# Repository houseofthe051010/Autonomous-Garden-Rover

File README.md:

# Autonomous Garden Rover

This is an open source outdoor garden robot that can mow grass and water plants for under $500. It features a powerful 3000 watt C6374 motor for mowing grass with electronic height control, and a large Nema17 turret system for watering at target places that supports a normal garden hose. The rover currently uses a 9 axis IMU + wheel encoders for autonomous function. The brain of this rover is a powerful ESP32-P4, which gives this rover the capability to listen and respond to commands using its built in microphone and speaker.

## Inspiration

I spend hours each week gardening and mowing grass. As someone into robotics, I realized I could build a garden rover to automate some of these repetitive chores. This project gave me a reason to learn more about robotics while building something useful for my yard.

[**Watch the full rover demo**](https://youtu.be/P-olpegfmmU) · [**Forge journal**](https://forge.hackclub.com/projects/3732) · [**See the assembly**](CAD/) · [**Watch the firmware demo**](https://www.youtube.com/watch?v=vQ5m_EN1jJQ) 

### CAD Render Assembly

## Features

* Under $500, anyone can build it
* All four wheels are motorized
* C6374 Motor offers 3000W+ of power, more than most commercial systems
* Nema17 planetary motors lift and raise the mower using a rope system.
* The turret system uses high reduction worm + dual stage planetary drives to shoot water
* Has a microphone and speaker and can run small ai vision/text recognition models
* Water flow can be controlled using a seperate esp32 controller
* Can be controlled from a phone or handheld controller
* Uses a 9axis imu and encoders on all four wheels for precise autonomous
* The aluminum chassis bends and acts as a suspension
* Supports raspberry pi 5 with ROS 2 as brain
* Supports a custom hand held controller from my previous FPV claw drone project
* Advanced flexibility for conneting new sensors, cameras, and electronics
* Water resistant

# Building it yourself

Go to [**INSTRUCTIONS.md**](INSTRUCTIONS.md) to see the complete build instructions.

## Block schematic

This is a block level schematic of how each system is split

Kicad: [`Schematics/Block-level schematic/`](Schematics/Block-level%20schematic/).

## Bill of materials

| Item                                                         | Qty. | Unit price |       Total | Link                                                                                                                 |
| ------------------------------------------------------------ | ---: | ---------: | ----------: | -------------------------------------------------------------------------------------------------------------------- |
| Waveshare ESP32-P4-WIFI6 development board                   |    1 |     $26.87 |      $26.87 | [Amazon](https://www.amazon.com/dp/B0FM3SPXZG)                                                                       |
| Steelworks 3/4 in x 8 ft aluminum channel                    |    2 |     $19.98 |      $39.96 | [Lowe's](https://www.lowes.com/pd/Steelworks-3-4-in-W-x-8-ft-L-Mill-Finished-Aluminum-Weldable-Trim-Channel/3058185) |
| LGXSHOP C6374 170KV sensored BLDC motor                      |    1 |     $29.50 |      $29.50 | [Amazon](https://www.amazon.com/dp/B0GR88K1XP)                                                                       |
| STM32F103C6T6 Blue Pill development board                    |    1 |      $1.75 |       $1.75 | [AliExpress](https://www.aliexpress.us/item/3256809531654480.html)                                                   |
| BTS7960 high-current motor driver board                      |    2 |      $5.56 |      $11.12 | [AliExpress](https://www.aliexpress.us/item/3256812145540065.html)                                                   |
| DS3230 PRO drivetrain servo motors (4-pack)                  |    1 |     $41.37 |      $41.37 | [AliExpress](https://www.aliexpress.us/item/3256808314550897.html)                                                   |
| STEPPERONLINE NEMA 17 stepper motors (3-pack)                |    1 |     $25.99 |      $25.99 | [Amazon](https://www.amazon.com/dp/B0B38GHRH8)                                                                       |
| Stepper controller board (12-24 VDC)                         |    1 |     $22.99 |      $22.99 | [Amazon](https://www.amazon.com/dp/B0CCVSMGXR)                                                                       |
| EONO PETG 3D printer filament 1 kg black                     |    2 |      $9.99 |      $19.98 | [Amazon](https://www.amazon.com/EONO3D-Printer-Filament-1-75mm-2-2lbs/dp/B0G2BQQ5RT)                                 |
| 608 sealed steel bearings (20-pack)                          |    1 |      $4.99 |       $4.99 | [Amazon](https://www.amazon.com/dp/B0GX14YCFF)                                                                       |
| M3 screw kit (420-piece)                                     |    1 |      $8.98 |       $8.98 | [Amazon](https://www.amazon.com/dp/B0CSWD34KJ)                                                                       |
| Flipsky ODESC 56 V v4.2 single-axis controller               |    1 |     $39.99 |      $39.99 | [Amazon](https://www.amazon.com/dp/B0CB64MVHC)                                                                       |
| 22 AWG wire (10 m)                                           |    1 |      $2.81 |       $2.81 | [AliExpress](https://www.aliexpress.us/item/3256801511977665.html)                                                   |
| 36 V 10.4 Ah lithium battery with charger and XT60 connector |    1 |     $79.99 |      $79.99 | [eBay](https://www.ebay.com/itm/318206384216)                                                                        |
| 20 A buck converter                                          |    2 |      $3.58 |       $7.16 | [AliExpress](https://www.aliexpress.us/item/3256808333733098.html)                                                   |
| XL4005 buck converter                                        |    1 |      $1.99 |       $1.99 | [AliExpress](https://www.aliexpress.us/item/3256808679872256.html)                                                   |
| MG996 servo motor                                            |    1 |      $3.44 |       $3.44 | [AliExpress](https://www.aliexpress.us/item/3256802804659030.html)                                                   |
| ESP32-WROOM-32 development board with U.FL                   |    1 |      $7.32 |       $7.32 | [AliExpress](https://www.aliexpress.us/item/3256807142919728.html)                                                   |
| BNO080/BNO085 9-DOF sensor module                            |    1 |     $18.99 |      $18.99 | [Amazon](https://www.amazon.com/dp/B0HCBRBZ76)                                                                       |
| Hello Hobby 3/8 in x 36 in wood dowel                        |    1 |      $0.78 |       $0.78 | [Walmart](https://www.walmart.com/ip/684374236)                                                                      |
| Tool Bench 40 ft diamond-braid rope with winder              |    1 |      $1.50 |       $1.50 | [Dollar Tree](https://www.dollartree.com/tool-bench-40-ft-diamond-braid-rope-with-winder-1-ct/295406)                |
| Seeed Studio XIAO ESP32S3 Sense                              |    1 |     $23.99 |      $23.99 | [Amazon](https://www.amazon.com/Seeed-Studio-XIAO-ESP32-Sense/dp/B0C69FFVHH)                                         |
| Quectel LC29HDA dual-frequency GPS module                     |    1 |     $28.74 |      $28.74 | [Walmart](https://www.walmart.com/ip/High-Precision-RTK-Base-Station-Board-Quectel-LC29H-Dual-Frequency-L1-L5-Positioning-Module-Output-RTCM-Data-LC29HDA/13958603097) |
| **Estimated total (priced items only)**                      |      |            | **$450.20** |                                                                                                                      |

## What I would do differently next time and plan for in the future

- Use stronger drivetrain motors to support a higher speed and better turning (though it would increase the price to build)
- Replace garden hose adapter system with a water tank onboard the rover
- Make a custom PCB that combines all the electronics and sub systems into one board with quick connectors for peripherals (much more expensive though)

## Repository Structure

In this repo, I have included everything needed to replicate and modify this project

- Firmware images and source code
- CAD source, assemblies, steps, and STLs
- Visual instruction manual
- Electrical schematics

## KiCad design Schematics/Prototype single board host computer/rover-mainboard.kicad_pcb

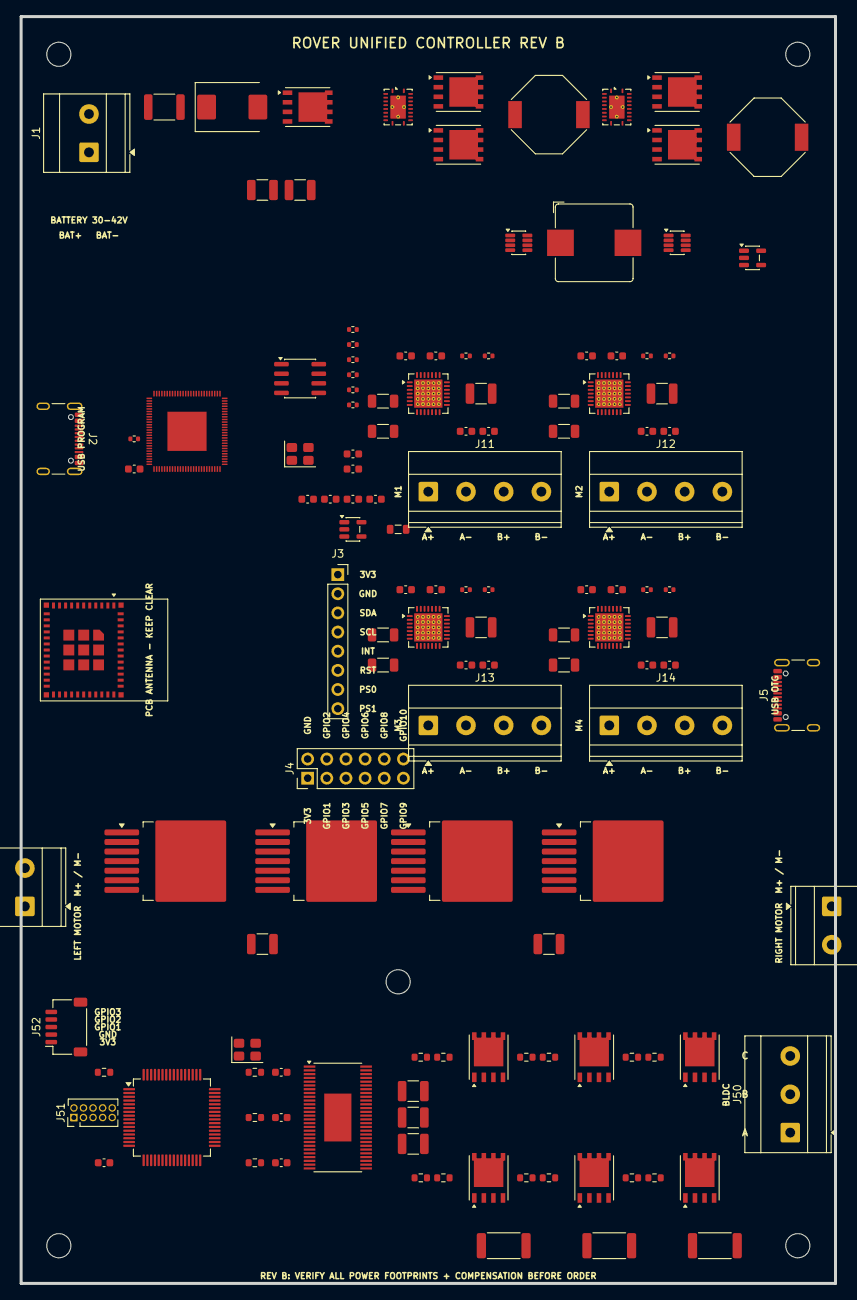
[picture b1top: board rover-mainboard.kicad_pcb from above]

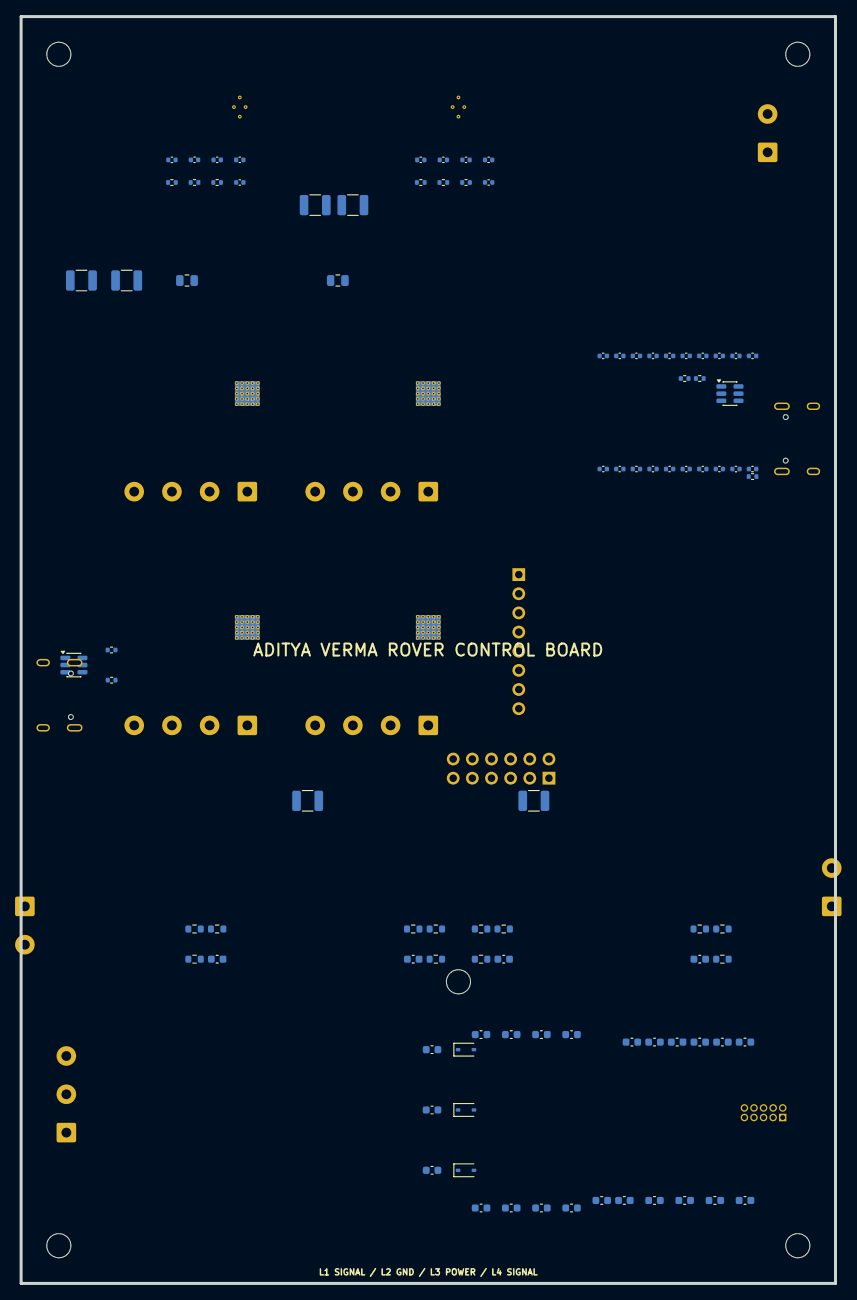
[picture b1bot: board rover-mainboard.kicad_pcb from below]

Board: 4 copper layers, 108.0 x 168.0 mm, 230 parts (93 on the bottom side), 10 nets, no tracks yet.

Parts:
C1B, C2B, C3B, C4B: 100uF 35V BULK; C_1210_3225Metric
C1C, C2C, C3C, C4C: 100nF VDD; C_0603_1608Metric
C1D, C2D, C3D, C4D, C326: 1uF VREG; C_0603_1608Metric
C1E, C2E, C3E, C4E: 100nF CP1-CP2; C_0603_1608Metric
C1F, C2F, C3F, C4F: 100nF VCP; C_0603_1608Metric
C40, C41: 2.2uF 100V INPUT; C_1210_3225Metric
C42, C43: 22uF 35V 24VOUT; C_1210_3225Metric
C44, C45: 47uF 16V 8VOUT; C_1210_3225Metric
C46: 22uF 10V 5VOUT; C_0805_2012Metric
C47: 22uF 6V3 3V3OUT; C_0805_2012Metric
C100, C101, C102, C103, C104, C105, C106, C107, C108, C109, C110, C111, C112, C113, C114, C115, C116, C117, C118, C119: 100nF P4 DECOUPLING; C_0402_1005Metric
C120: 10uF VDD_LDO; C_0603_1608Metric
C121: 10uF VDD_DCDCC; C_0603_1608Metric
C122: 4.7uF USBPHY; C_0603_1608Metric
C123: 1uF FLASHIO; C_0603_1608Metric
C124: 10nF USBPHY; C_0603_1608Metric
C125: 10uF VDD_BAT; C_0603_1608Metric
C126: 1uF CHIP_PU; C_0603_1608Metric
C200, C208: 100nF VCC; C_0402_1005Metric
C201, C209: 100nF BST; C_0402_1005Metric
C202, C210: 1uF SS; C_0402_1005Metric
C203, C211: 1nF COMP; C_0402_1005Metric
C204, C212: 100pF COMP; C_0402_1005Metric
C300, C320: 470nF BTN SUPPLY; C_1210_3225Metric
C300#2, C301#2, C302#2, C303#2, C304, C305: 100nF; C_0603_1608Metric
C301, C321: 220uF 16V DRIVE BULK; C_1210_3225Metric
C302, C303, C322#2, C323#2: 1nF IS FILTER; C_0603_1608Metric
C306, C307: 2.2uF VCAP; C_0603_1608Metric
C308: 4.7uF VDDA; C_0603_1608Metric
C309: 100nF VDDA; C_0603_1608Metric
C310, C311: 18pF XTAL; C_0603_1608Metric
C312: 100nF NRST; C_0603_1608Metric
C320#2: 1uF GVDD; C_0603_1608Metric
C321#2: 100nF DVDD; C_0603_1608Metric
C322: 2.2uF AVDD; C_0603_1608Metric
C323, C327: 10uF PVDD; C_0603_1608Metric
C324: 10nF CP1; C_0603_1608Metric
C325: 100nF CP2; C_0603_1608Metric
C331, C332, C333: 100nF BOOTSTRAP; C_0603_1608Metric
C340, C341, C342: 120uF 50V BLDC BUS; C_1210_3225Metric
CCS51, CCS52, CCS53: 1nF CURRENT SENSE; C_0603_1608Metric
D1: SMCJ48A TVS; D_SMC
D10: USB FS ESD ARRAY; SOT-23-6
D11: USB HS LOW-C ESD; SOT-23-6
D51, D52, D53: 60V BOOTSTRAP; D_SOD-323
F1: 15A INPUT FUSE; Fuse_1812_4532Metric
H1, H2, H3, H4, H5: M3; MountingHole_3.2mm_M3
J1: 10S BATTERY; TerminalBlock_Phoenix_MKDS-3-2-5.08_1x02_P5.08mm_Horizontal
J2: USB-C PROGRAM/DEBUG; USB_C_Receptacle_GCT_USB4105-xx-A_16P_TopMnt_Horizontal
J3: BNO080 BREAKOUT; PinSocket_1x08_P2.54mm_Vertical
J4: OPEN GPIO; PinHeader_2x06_P2.54mm_Vertical
J5: USB-C OTG HIGH SPEED; USB_C_Receptacle_GCT_USB4105-xx-A_16P_TopMnt_Horizontal
J11: STEPPER 1: A+ A- B+ B-; TerminalBlock_Phoenix_MKDS-1,5-4_1x04_P5.00mm_Horizontal
J12: STEPPER 2: A+ A- B+ B-; TerminalBlock_Phoenix_MKDS-1,5-4_1x04_P5.00mm_Horizontal
J13: STEPPER 3: A+ A- B+ B-; TerminalBlock_Phoenix_MKDS-1,5-4_1x04_P5.00mm_Horizontal
J14: STEPPER 4: A+ A- B+ B-; TerminalBlock_Phoenix_MKDS-1,5-4_1x04_P5.00mm_Horizontal
J30: LEFT MOTOR; TerminalBlock_Phoenix_MKDS-3-2-5.08_1x02_P5.08mm_Horizontal
J32: RIGHT MOTOR; TerminalBlock_Phoenix_MKDS-3-2-5.08_1x02_P5.08mm_Horizontal
J50: BLDC U V W; TerminalBlock_Phoenix_MKDS-3-3-5.08_1x03_P5.08mm_Horizontal
J51: STM32 SWD; PinHeader_2x05_P1.27mm_Vertical
J52: ODESC AUX 3V3 GND IO1 IO2 IO3; JST_SH_SM05B-SRSS-TB_1x05-1MP_P1.00mm_Horizontal
L13: 2.2uH P4 CORE; L_0805_2012Metric
L40: 10uH 24V; L_Bourns-SRU1028_10.0x10.0mm
L41: 6.8uH 8V; L_Bourns-SRU1028_10.0x10.0mm
L42: 4.7uH 5V; L_Bourns_SRP1038C_10.0x10.0mm
Q1: 80V REVERSE-POLARITY FET; PowerPAK_SO-8_Single
Q40, Q41: NVMFS6B14NLT1G 100V BUCK; PowerPAK_SO-8_Single
Q42, Q43, Q50, Q51, Q52, Q53, Q54, Q55: NTMFS5C628NLT1G 60V MOSFET; PowerPAK_SO-8_Single
R1A, R1B, R2A, R2B, R3A, R3B, R4A, R4B: 0.10R SENSE; R_1206_3216Metric
R1C, R2C, R3C, R4C: 100k ENABLE PD; R_0402_1005Metric
R1D, R2D, R3D, R4D: 100k STEP PD; R_0402_1005Metric
R30A, R30C, R32A, R32C: 10k IN PD; R_0603_1608Metric
R30B, R30D, R32B, R32D: 10k INH PD; R_0603_1608Metric
R30E, R30F, R32E, R32F: 1k IS FILTER; R_0603_1608Metric
R100: 10k CHIP_PU; R_0402_1005Metric
R101: 10k BOOT; R_0402_1005Metric
R102, R103, R104, R105, R106, R107: 0R FLASH TUNING; R_0402_1005Metric
R110, R111, R112, R113: 22R USB SERIES; R_0402_1005Metric
R205, R213: 10k FB; R_0402_1005Metric
R206: 287k FB24; R_0402_1005Metric
R207, R215: 10R GATE; R_0402_1005Metric
R214: 90.9k FB8; R_0402_1005Metric
R300: 10k NRST; R_0603_1608Metric
RCS51, RCS52, RCS53: 20R CURRENT SENSE; R_0603_1608Metric
RG51, RG52, RG53, RG54, RG55, RG56: 2.2R GATE; R_0603_1608Metric
RPD51, RPD52, RPD53, RPD54, RPD55, RPD56: 100k GATE PD; R_0603_1608Metric
RSH50, RSH51, RSH52: 0.5mR 3W; R_2512_6332Metric
U10: ESP32-P4NRW32X QFN104
U11: W25Q128JVSIQ; SOIC-8_3.9x4.9mm_P1.27mm
U12: ESP32-C6-MINI-1-H4 PCB ANTENNA; ESP32-C6-MINI-1
U13: TLV62569 P4 CORE DCDC; SOT-23-5
U21: A4988SETTR-T AXIS1; QFN-28-1EP_5x5mm_P0.5mm_EP3.75x3.75mm_ThermalVias
U22: A4988SETTR-T AXIS2; QFN-28-1EP_5x5mm_P0.5mm_EP3.75x3.75mm_ThermalVias
U23: A4988SETTR-T AXIS3; QFN-28-1EP_5x5mm_P0.5mm_EP3.75x3.75mm_ThermalVias
U24: A4988SETTR-T AXIS4; QFN-28-1EP_5x5mm_P0.5mm_EP3.75x3.75mm_ThermalVias
U30: BTN7960B LEFT HALF-A; TO-263-7_TabPin4
U31: BTN7960B LEFT HALF-B; TO-263-7_TabPin4
U32: BTN7960B RIGHT HALF-A; TO-263-7_TabPin4
U33: BTN7960B RIGHT HALF-B; TO-263-7_TabPin4
U40: LM5146 42V->24V; Texas_RGY_R-PVQFN-N20_EP2.05x3.05mm_ThermalVias
U41: LM5146 24V->8V; Texas_RGY_R-PVQFN-N20_EP2.05x3.05mm_ThermalVias
U42: MP2315 8V->5V 3A; TSOT-23-8
U43: MP2315 5V->3V3 3A; TSOT-23-8
U44: AP2112 3V3 SENSOR LDO; SOT-23-5
U50: STM32F405RGT6; LQFP-64_10x10mm_P0.5mm
U51: DRV8301DCAR; HTSSOP-56-1EP_6.1x14mm_P0.5mm_EP3.61x6.35mm
Y1: 40MHz; Crystal_SMD_3225-4Pin_3.2x2.5mm
Y50: 8MHz STM32; Crystal_SMD_3225-4Pin_3.2x2.5mm

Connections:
+3V3_LOGIC: J4.1, J52.1, U21.18, U22.18, U23.18, U24.18
+5V_LOGIC: J2.A4, J2.A9, J2.B4, J2.B9, J5.A4, J5.A9, J5.B4, J5.B9, U21.17, U22.17, U23.17, U24.17
+8V_DRIVE: U30.5, U31.5, U32.5, U33.5
+24V_STEPPER: U21.10, U22.10, U23.10, U24.10
GND: D1.2, J1.2, J2.A1, J2.A12, J2.B1, J2.B12, J3.2, J4.2, J5.A1, J5.A12, J5.B1, J5.B12, J52.2, U21.8, U21.9, U21.29, U22.8, U22.9, U22.29, U23.8, U23.9, U23.29, U24.8, U24.9, U24.29, U30.1, U31.1, U32.1, U33.1
J2_USB_DM: J2.A7, J2.B7
J2_USB_DP: J2.A6, J2.B6
J5_USB_DM: J5.A7, J5.B7
J5_USB_DP: J5.A6, J5.B6
VBAT_10S_30_42V: D1.1, F1.1, F1.2, J1.1
